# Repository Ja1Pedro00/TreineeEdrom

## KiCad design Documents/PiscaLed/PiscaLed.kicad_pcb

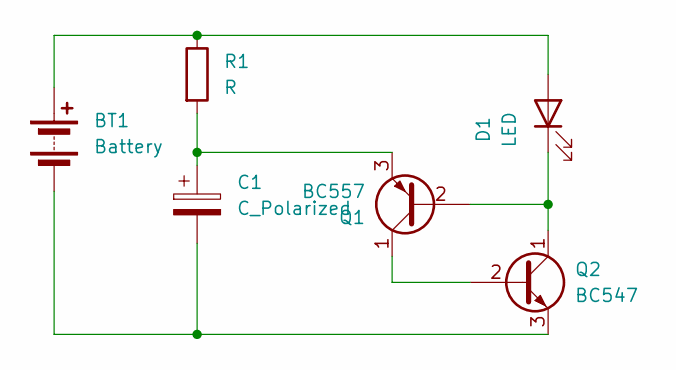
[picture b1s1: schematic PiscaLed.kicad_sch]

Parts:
BT1: Battery; BatteryHolder_Keystone_107_1x23mm
C1: C_Polarized; CP_Radial_D5.0mm_P2.50mm
D1: LED; LED_D3.0mm
Q1: BC557; TO-92_Inline
Q2: BC547; TO-92_Inline
R1: R; R_Axial_DIN0204_L3.6mm_D1.6mm_P7.62mm_Horizontal

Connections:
unnamed: BT1.1 (+), D1.2 (A), R1.1
unnamed: BT1.2 (-), C1.2, Q2.3 (E)
unnamed: D1.1 (K), Q1.2 (B), Q2.1 (C)
unnamed: Q1.1 (C), Q2.2 (B)
unnamed: C1.1, Q1.3 (E), R1.2

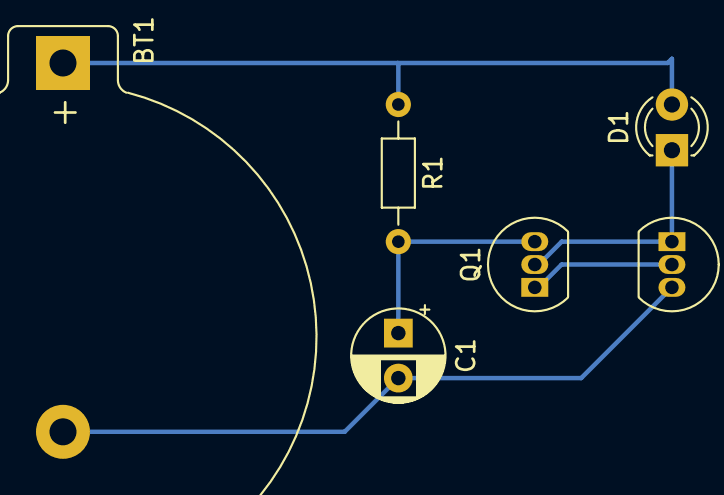
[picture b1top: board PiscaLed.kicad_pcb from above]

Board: 2 copper layers, 6 parts (0 on the bottom side), 5 nets.

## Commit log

2023-11-30 Print da primeira tarefa
2023-11-30 Print da primeira Tarefa (correção)
2023-12-14 envio programa Behaviour
2023-12-14 Lançamento de TesteBehaviour
2023-12-22 Progrma corrigido Teste1
2024-01-04 Primeira Tarefa da Visao
2024-01-12 Tarefa eletrica
2024-01-15 Simulaçao de estruturas de Coxa e Quadril
2024-01-16 Delete TesteBehaviour.ipynb
    organização de branches
2024-01-16 Delete Documents/Visao1.py
    Organização de branches
2024-01-16 Delete Documents directory
    Organização de branches
2024-01-16 Criação de branch Movimento
2024-01-20 Segunda Tarefa Behaviour (maquina de estados)
2024-01-20 Delete Documents/Edrom directory
    Organização
2024-01-22 Delete Documents/Visao1.py
    correção de atividade
2024-01-22 Create Tarefa_1_Visao
    Tarefa corrigida
2024-02-02 Tarefas de Python
2024-02-02 Segunda Trefa Visao
2024-02-02 Delete Visao directory
    Organização
2024-02-02 Revert "Delete Documents/Visao1.py"
    This reverts commit 9e7d8698ebbdcbd43a81f0735a83877ee6b9e1e9.
2024-02-02 Segunda Tarefa Visao
2024-02-02 Delete Documents directory
    Organização
2024-02-02 Terceira tarefa Visao
2024-02-02 Terceita Tarefa Visao
2024-02-02 Rename Tarefa_1_Visao to Tarefa_1_Visao.py
    adição de extensao ".py"
2024-02-03 Prints ROS2
